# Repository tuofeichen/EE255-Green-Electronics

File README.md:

# EE255-Green-Electronics
This is the repo for the course project for EE 255 Green Electronics at Stanford. We built a prototype AC-AC converter system for load side demand response. 

Please see the below website for more information about the project. 
https://ee155powerprofiler.weebly.com

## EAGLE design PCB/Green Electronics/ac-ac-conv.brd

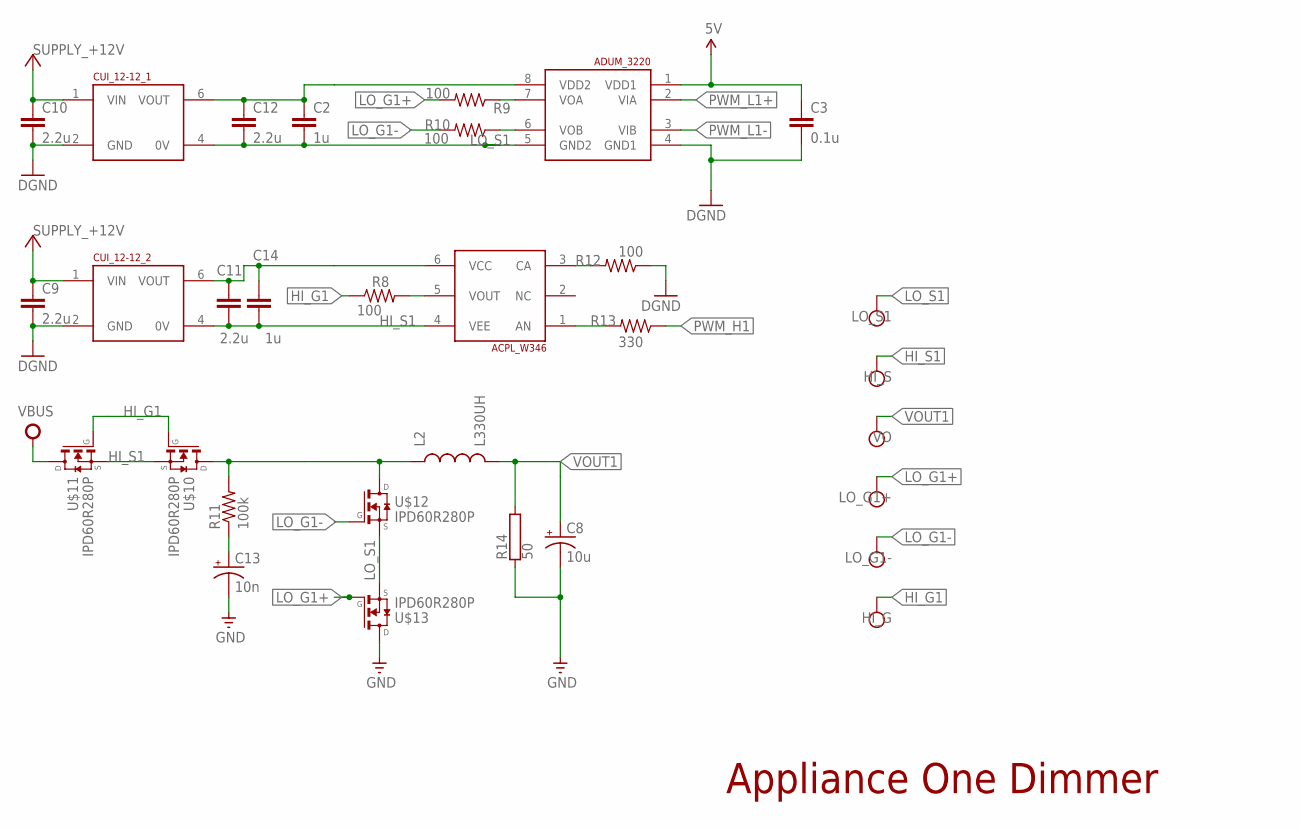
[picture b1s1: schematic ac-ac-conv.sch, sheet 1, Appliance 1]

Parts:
ACPL_W346: ACPL-W346-SSO6; SSO-6
ADUM_3220: ADUM3220; SO08
C2, C14: 1u; 0603-CAP
C3: 0.1u; 0603-CAP
C8: 10u; PANASONIC_C
C9, C10, C11, C12: 2.2u; 0603-CAP
C13: 10n; EIA3216
CUI_12-12_1, CUI_12-12_2: CUI-S12-S12; CUI_PDM2
HI_G: TESTPOINT0.1"; 1X01_ROUND
HI_S: TESTPOINT0.1"; 1X01_ROUND
L2: L330UH; BOUNRS_330UH
LO_G1+, LO_G1-: TESTPOINT0.1"; 1X01_ROUND
LO_S1: TESTPOINT0.1"; 1X01_ROUND
R8, R9, R10, R12: 100; 0603-RES
R11: 100k; R2512
R13: 330; 0603-RES
R14: 50; TO-247-2V
U$10, U$11, U$12, U$13: IPD60R280P; DPAK
VO: TESTPOINT0.1"; 1X01_ROUND

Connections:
5V: ADUM_3220.1 (VDD1), C3.1; also elsewhere on the board
+12V: C9.1, C10.1, CUI_12-12_1.1 (VIN), CUI_12-12_2.1 (VIN); also elsewhere on the board
GND: ADUM_3220.4 (GND1), C3.2, C8.-, C9.2, C10.2, C13.C (-), CUI_12-12_1.2 (GND), CUI_12-12_2.2 (GND), R12.1, R14.1, U$13.4 (D); also elsewhere on the board
HI_G1: HI_G.1, R8.1, U$10.1 (G), U$11.1 (G)
HI_PS1: ACPL_W346.6 (VCC), C11.1, C14.1, CUI_12-12_2.6 (VOUT)
HI_S1: ACPL_W346.4 (VEE), C11.2, C14.2, CUI_12-12_2.4 (0V), HI_S.1, U$10.3 (S), U$11.3 (S)
LO_G1+: LO_G1+.1, R9.2, U$13.1 (G)
LO_G1-: LO_G1-.1, R10.2, U$12.1 (G)
LO_PS1: ADUM_3220.8 (VDD2), C2.1, C12.1, CUI_12-12_1.6 (VOUT)
LO_S1: ADUM_3220.5 (GND2), C2.2, C12.2, CUI_12-12_1.4 (0V), LO_S1.1, U$12.3 (S), U$13.3 (S)
unnamed: L2.P$1 (1), R11.2, U$10.4 (D), U$12.4 (D)
unnamed: C13.A (+), R11.1
unnamed: ACPL_W346.3 (CA), R12.2
unnamed: ACPL_W346.1 (AN), R13.2
unnamed: ADUM_3220.7 (VOA), R9.1
unnamed: ADUM_3220.6 (VOB), R10.1
PWM_H1: R13.1; also elsewhere on the board
PWM_L1+: ADUM_3220.2 (VIA); also elsewhere on the board
PWM_L1-: ADUM_3220.3 (VIB); also elsewhere on the board
VBUS: U$11.4 (D); also elsewhere on the board
VOUT1: C8.+, L2.P$2 (2), R14.2, VO.1; also elsewhere on the board
VOUT_H2: ACPL_W346.5 (VOUT), R8.2

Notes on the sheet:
Appliance One Dimmer

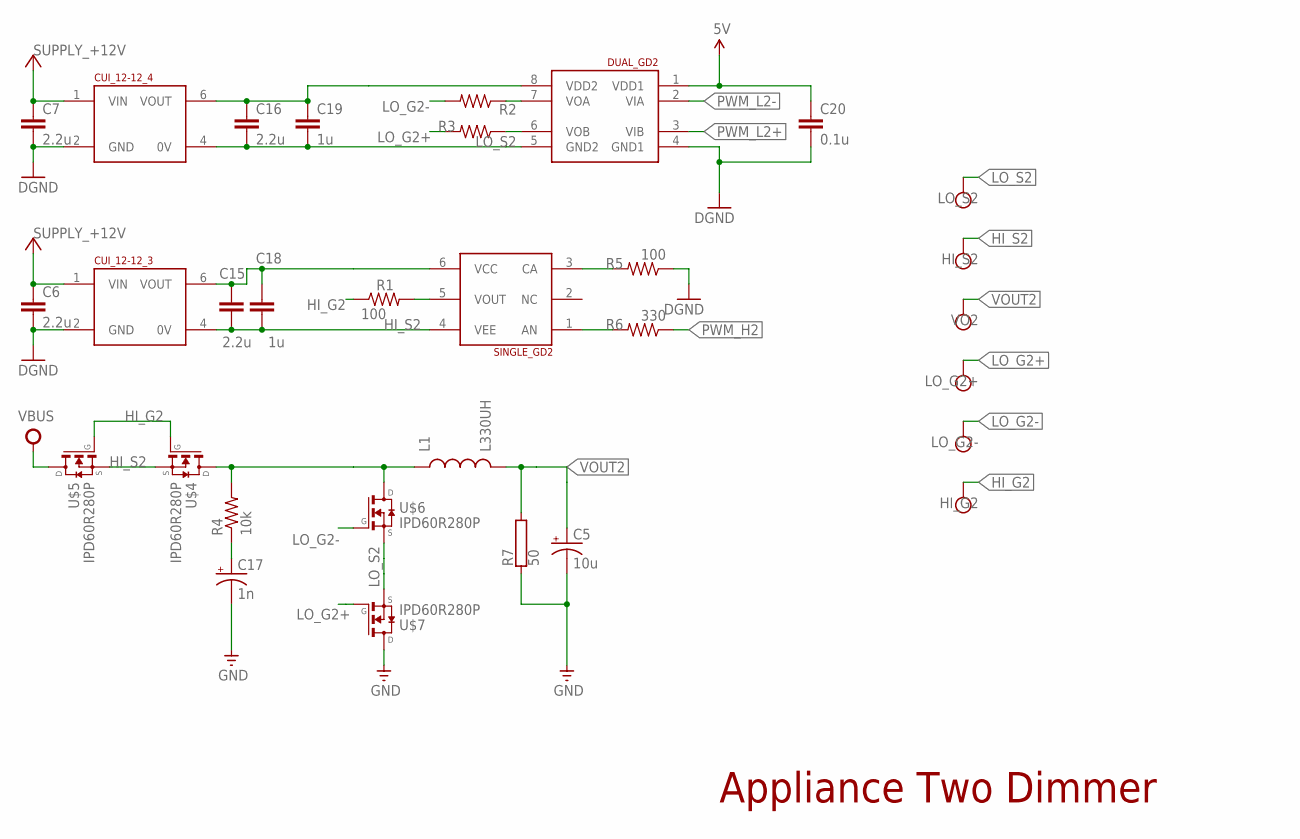
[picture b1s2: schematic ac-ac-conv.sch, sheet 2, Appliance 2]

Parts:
C5: 10u; PANASONIC_C
C6, C7, C15, C16: 2.2u; 0603-CAP
C17: 1n; EIA3216
C18, C19: 1u; 0603-CAP
C20: 0.1u; 0603-CAP
CUI_12-12_3, CUI_12-12_4: CUI-S12-S12; CUI_PDM2
DUAL_GD2: ADUM3220; SO08
HI_G2: TESTPOINT0.1"; 1X01_ROUND
HI_S2: TESTPOINT0.1"; 1X01_ROUND
L1: L330UH; BOUNRS_330UH
LO_G2+, LO_G2-: TESTPOINT0.1"; 1X01_ROUND
LO_S2: TESTPOINT0.1"; 1X01_ROUND
R1, R5: 100; 0603-RES
R2, R3: RESISTOR0603-RES; 0603-RES
R4: 10k; R2512
R6: 330; 0603-RES
R7: 50; TO-247-2V
SINGLE_GD2: ACPL-W346-SSO6; SSO-6
U$4, U$5, U$6, U$7: IPD60R280P; DPAK
VO2: TESTPOINT0.1"; 1X01_ROUND

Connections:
5V: C20.1, DUAL_GD2.1 (VDD1); also elsewhere on the board
+12V: C6.1, C7.1, CUI_12-12_3.1 (VIN), CUI_12-12_4.1 (VIN); also elsewhere on the board
GND: C5.-, C6.2, C7.2, C17.C (-), C20.2, CUI_12-12_3.2 (GND), CUI_12-12_4.2 (GND), DUAL_GD2.4 (GND1), R5.1, R7.1, U$7.4 (D); also elsewhere on the board
HI_G2: HI_G2.1, R1.1, U$4.1 (G), U$5.1 (G)
HI_PS2: C15.1, C18.1, CUI_12-12_3.6 (VOUT), SINGLE_GD2.6 (VCC)
HI_S2: C15.2, C18.2, CUI_12-12_3.4 (0V), HI_S2.1, SINGLE_GD2.4 (VEE), U$4.3 (S), U$5.3 (S)
LO_G2+: LO_G2+.1, R3.2, U$7.1 (G)
LO_G2-: LO_G2-.1, R2.2, U$6.1 (G)
LO_PS2: C16.1, C19.1, CUI_12-12_4.6 (VOUT), DUAL_GD2.8 (VDD2)
LO_S2: C16.2, C19.2, CUI_12-12_4.4 (0V), DUAL_GD2.5 (GND2), LO_S2.1, U$6.3 (S), U$7.3 (S)
unnamed: L1.P$1 (1), R4.2, U$4.4 (D), U$6.4 (D)
unnamed: C17.A (+), R4.1
unnamed: R5.2, SINGLE_GD2.3 (CA)
unnamed: R6.2, SINGLE_GD2.1 (AN)
unnamed: DUAL_GD2.7 (VOA), R2.1
unnamed: DUAL_GD2.6 (VOB), R3.1
PWM_H2: R6.1; also elsewhere on the board
PWM_L2+: DUAL_GD2.3 (VIB); also elsewhere on the board
PWM_L2-: DUAL_GD2.2 (VIA); also elsewhere on the board
VBUS: U$5.4 (D); also elsewhere on the board
VOUT2: C5.+, L1.P$2 (2), R7.2, VO2.1; also elsewhere on the board
VOUT_H1: R1.2, SINGLE_GD2.5 (VOUT)

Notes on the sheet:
Appliance Two Dimmer

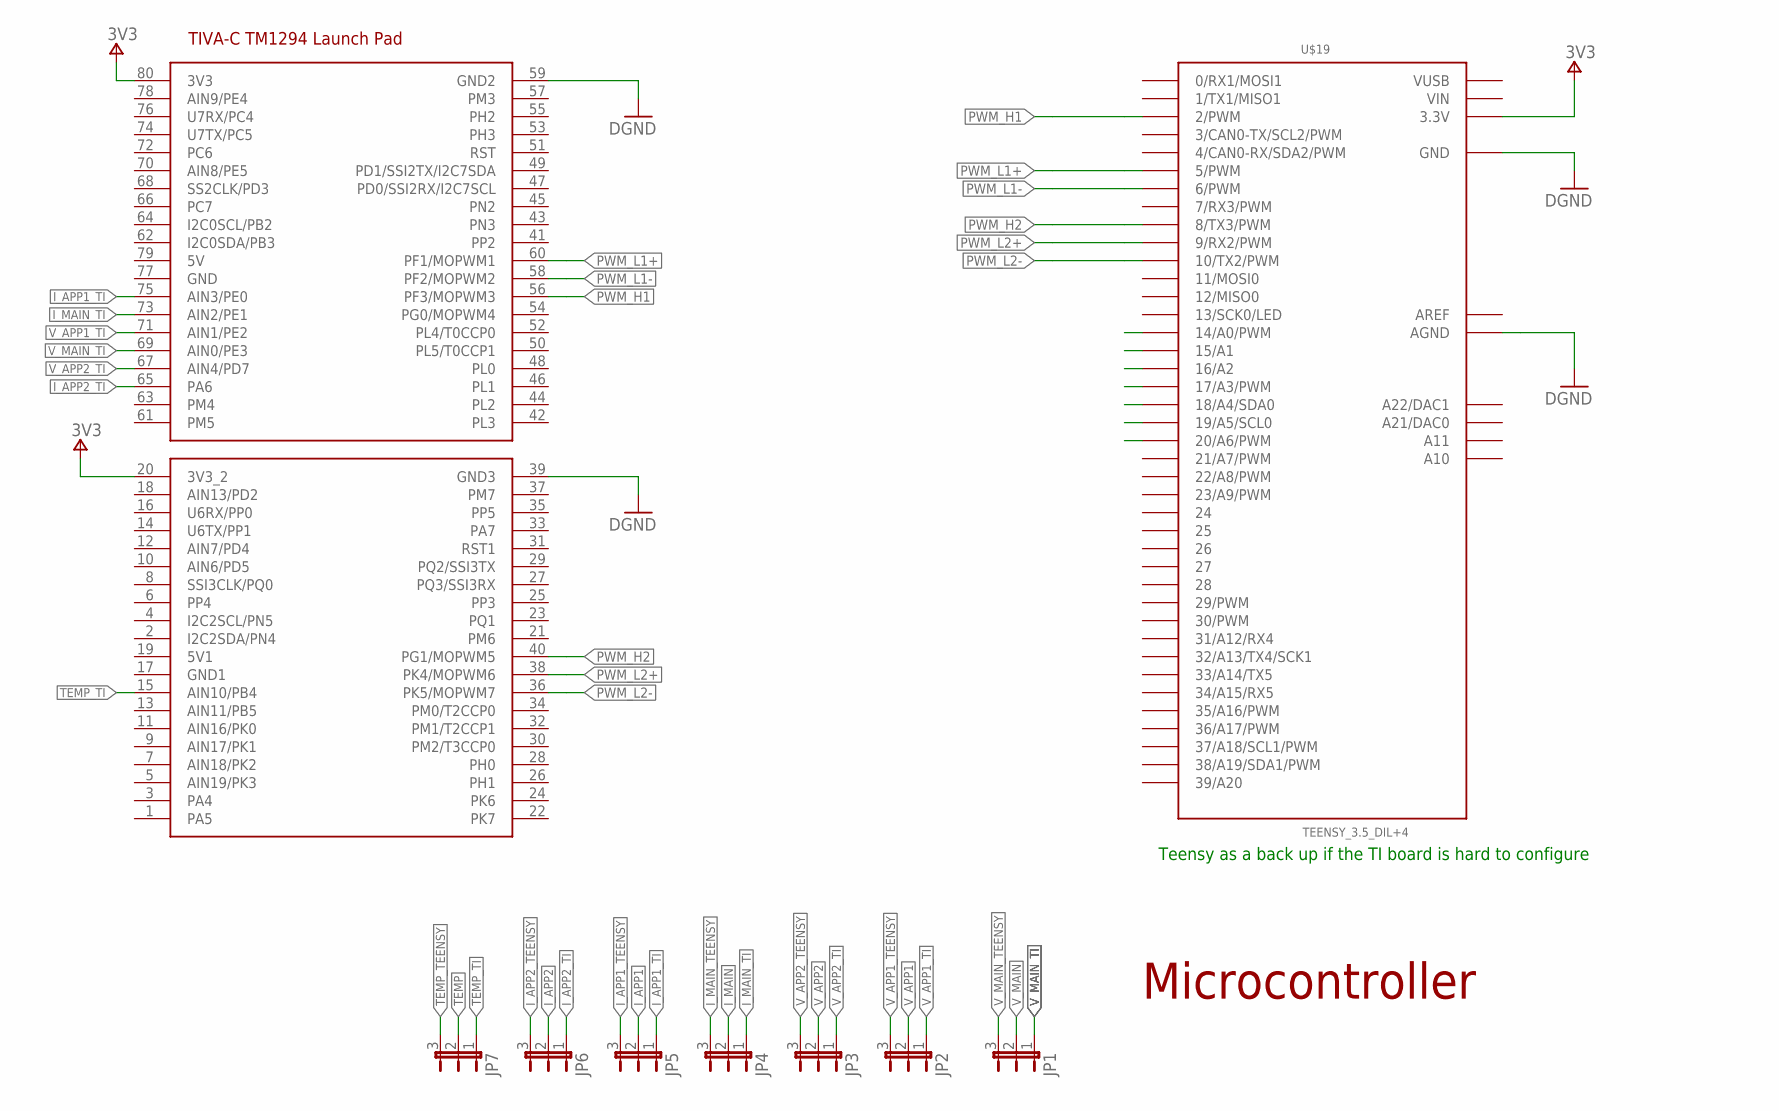
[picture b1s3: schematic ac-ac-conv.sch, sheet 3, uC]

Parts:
JP1, JP2, JP3, JP4, JP5, JP6, JP7: JUMPER-3SMD; SJ_3
U$17: TM4C1294_SHIELD; TIVA-C-LP-BOOSTER-PACK
U$19: TEENSY_3.5_DIL+4

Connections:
3V3: U$17.20 (3V3_2), U$17.80 (3V3), U$19.3.3V, U$19.3.3V3 (3.3V); also elsewhere on the board
AREF: U$19.AREF
GND: U$17.39 (GND3), U$17.59 (GND2), U$19.AGND, U$19.GND, U$19.GND1 (GND); also elsewhere on the board
I_APP1: JP5.2; also elsewhere on the board
I_APP1_TEENSY: JP5.3
I_APP1_TI: JP5.1, U$17.75 (AIN3/PE0)
I_APP2: JP6.2; also elsewhere on the board
I_APP2_TEENSY: JP6.3
I_APP2_TI: JP6.1, U$17.65 (PA6)
I_MAIN: JP4.2; also elsewhere on the board
I_MAIN_TEENSY: JP4.3
I_MAIN_TI: JP4.1, U$17.73 (AIN2/PE1)
PWM_H1: U$17.56 (PF3/MOPWM3), U$19.2 (2/PWM); also elsewhere on the board
PWM_H2: U$17.40 (PG1/MOPWM5), U$19.8 (8/TX3/PWM); also elsewhere on the board
PWM_L1+: U$17.60 (PF1/MOPWM1), U$19.5 (5/PWM); also elsewhere on the board
PWM_L1-: U$17.58 (PF2/MOPWM2), U$19.6 (6/PWM); also elsewhere on the board
PWM_L2+: U$17.38 (PK4/MOPWM6), U$19.9 (9/RX2/PWM); also elsewhere on the board
PWM_L2-: U$17.36 (PK5/MOPWM7), U$19.10 (10/TX2/PWM); also elsewhere on the board
TEMP: JP7.2; also elsewhere on the board
TEMP_TEENSY: JP7.3
TEMP_TI: JP7.1, U$17.15 (AIN10/PB4)
VIN: U$19.VIN
VUSB: U$19.VUSB
V_APP1: JP2.2; also elsewhere on the board
V_APP1_TEENSY: JP2.3
V_APP1_TI: JP2.1, U$17.71 (AIN1/PE2)
V_APP2: JP3.2; also elsewhere on the board
V_APP2_TEENSY: JP3.3
V_APP2_TI: JP3.1, U$17.67 (AIN4/PD7)
V_MAIN: JP1.2; also elsewhere on the board
V_MAIN_TEENSY: JP1.3
V_MAIN_TI: JP1.1, U$17.69 (AIN0/PE3)

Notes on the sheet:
Teensy as a back up if the TI board is hard to configure
Microcontroller

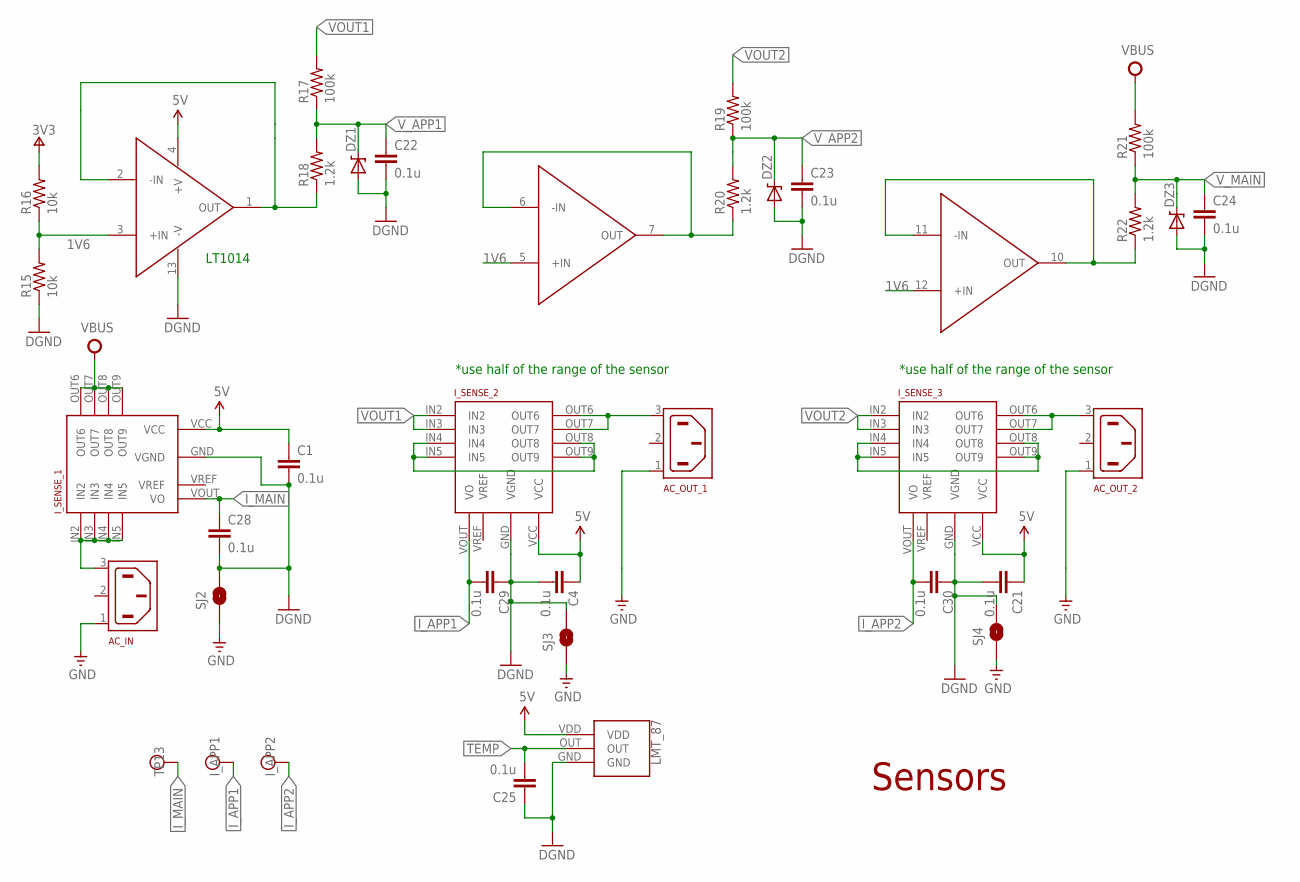
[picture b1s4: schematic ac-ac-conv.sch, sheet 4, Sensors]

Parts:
AC_IN: 6ESRM-P
AC_OUT_1, AC_OUT_2: 6ESRM-P
C1, C4, C21, C22, C23, C24, C25, C28, C29, C30: 0.1u; 0603-CAP
DZ1, DZ2, DZ3: DIODE-ZENER-BZT52; SOD-323
I_APP1, I_APP2: TESTPOINT0.1"; 1X01_ROUND
I_SENSE_1, I_SENSE_2, I_SENSE_3: F03PS05; F03P_THRU_HOLE
LMT_87: LMT87_PAC; LMT87_TO
R15, R16: 10k; 0603-RES
R17, R19, R21: 100k; 1206
R18, R20, R22: 1.2k; 1206
SJ2, SJ3, SJ4: SOLDERJUMPERNC2; SJ_2S-NOTRACE
TP13: TESTPOINT0.1"; 1X01_ROUND
U$15: LT1014; SO16L

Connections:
1V6: R15.2, R16.1, U$15.3 (+IN), U$15.5 (+IN), U$15.12 (+IN)
3V3: R16.2; also elsewhere on the board
5V: C1.1, C4.1, C21.1, I_SENSE_1.VCC, I_SENSE_2.VCC, I_SENSE_3.VCC, LMT_87.VDD, U$15.4 (+V); also elsewhere on the board
+IN: U$15.14 (+IN)
-IN: U$15.15 (-IN)
DGND: C1.2, C4.2, C21.2, C28.2, C29.1, C30.1, I_SENSE_1.GND (VGND), I_SENSE_2.GND (VGND), I_SENSE_3.GND (VGND), SJ2.2, SJ3.2, SJ4.2
GND: AC_IN.1 (AC1), AC_OUT_1.1 (AC1), AC_OUT_2.1 (AC1), C22.2, C23.2, C24.2, C25.1, DZ1.2 (A), DZ2.2 (A), DZ3.2 (A), LMT_87.GND, R15.1, SJ2.1, SJ3.1, SJ4.1, U$15.13 (-V); also elsewhere on the board
I_APP1: C29.2, I_APP1.1, I_SENSE_2.VOUT (VO); also elsewhere on the board
I_APP2: C30.2, I_APP2.1, I_SENSE_3.VOUT (VO); also elsewhere on the board
I_MAIN: C28.1, I_SENSE_1.VOUT (VO), TP13.1; also elsewhere on the board
unnamed: AC_IN.3 (AC2), I_SENSE_1.IN2, I_SENSE_1.IN3, I_SENSE_1.IN4, I_SENSE_1.IN5
unnamed: I_SENSE_2.IN4, I_SENSE_2.IN5, I_SENSE_2.OUT8, I_SENSE_2.OUT9
unnamed: I_SENSE_3.IN4, I_SENSE_3.IN5, I_SENSE_3.OUT8, I_SENSE_3.OUT9
unnamed: AC_OUT_1.3 (AC2), I_SENSE_2.OUT6, I_SENSE_2.OUT7
unnamed: AC_OUT_2.3 (AC2), I_SENSE_3.OUT6, I_SENSE_3.OUT7
unnamed: R18.1, U$15.1 (OUT), U$15.2 (-IN)
unnamed: R22.1, U$15.10 (OUT), U$15.11 (-IN)
unnamed: R20.1, U$15.6 (-IN), U$15.7 (OUT)
OUT: U$15.16 (OUT)
TEMP: C25.2, LMT_87.OUT; also elsewhere on the board
VBUS: I_SENSE_1.OUT6, I_SENSE_1.OUT7, I_SENSE_1.OUT8, I_SENSE_1.OUT9, R21.2; also elsewhere on the board
VOUT1: I_SENSE_2.IN2, I_SENSE_2.IN3, R17.2; also elsewhere on the board
VOUT2: I_SENSE_3.IN2, I_SENSE_3.IN3, R19.2; also elsewhere on the board
V_APP1: C22.1, DZ1.1 (C), R17.1, R18.2; also elsewhere on the board
V_APP2: C23.1, DZ2.1 (C), R19.1, R20.2; also elsewhere on the board
V_MAIN: C24.1, DZ3.1 (C), R21.1, R22.2; also elsewhere on the board

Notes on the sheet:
*use half of the range of the sensor
LT1014
Sensors

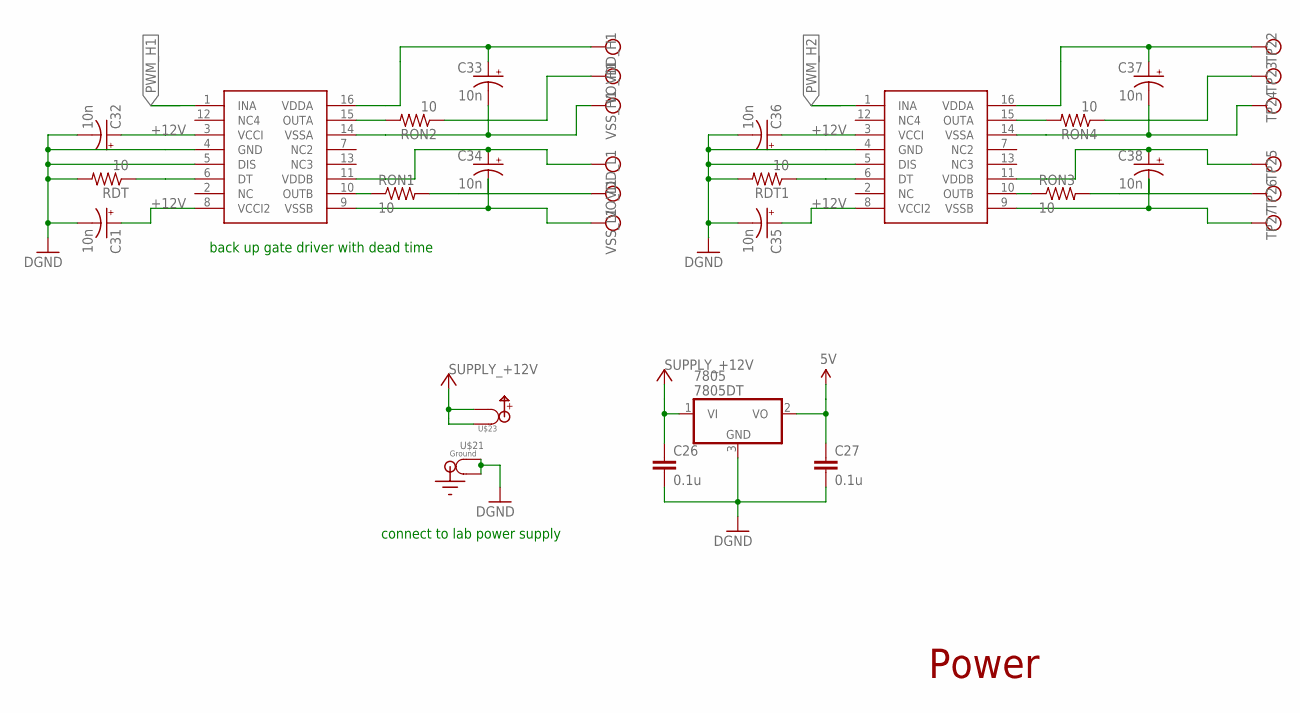
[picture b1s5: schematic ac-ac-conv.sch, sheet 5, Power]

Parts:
7805: 7805DT; TO252
C26, C27: 0.1u; 0603-CAP
C31, C32, C33, C34, C35, C36, C37, C38: 10n; EIA3216
RDT, RDT1: 10; 0603-RES
RON1, RON2, RON3, RON4: 10; 0603-RES
TP22, TP23, TP24, TP25, TP26, TP27: TESTPOINT0.1"; 1X01_ROUND
U$1, U$9: UCC20520; SO16
U$21: SPADE-GROUND
U$23: SPADE-POWER
VDD_H1: TESTPOINT0.1"; 1X01_ROUND
VDD_L1: TESTPOINT0.1"; 1X01_ROUND
VO_H1: TESTPOINT0.1"; 1X01_ROUND
VO_L1: TESTPOINT0.1"; 1X01_ROUND
VSS_H1: TESTPOINT0.1"; 1X01_ROUND
VSS_L1: TESTPOINT0.1"; 1X01_ROUND

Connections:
5V: 7805.2 (VO), C27.1; also elsewhere on the board
+12V: 7805.1 (VI), C26.1, C31.A (+), C32.A (+), C35.A (+), C36.A (+), U$1.3 (VCCI), U$1.8 (VCCI2), U$9.3 (VCCI), U$9.8 (VCCI2), U$23.P$1, U$23.P$2; also elsewhere on the board
GND: 7805.3 (GND), C26.2, C27.2, C31.C (-), C32.C (-), C35.C (-), C36.C (-), RDT.2, RDT1.2, U$1.4 (GND), U$1.5 (DIS), U$9.4 (GND), U$9.5 (DIS), U$21.P$1, U$21.P$2; also elsewhere on the board
unnamed: C33.A (+), U$1.16 (VDDA), VDD_H1.1
unnamed: RON1.1, U$1.10 (OUTB)
unnamed: RDT.1, U$1.6 (DT)
unnamed: C33.C (-), U$1.14 (VSSA), VSS_H1.1
unnamed: C34.A (+), U$1.11 (VDDB), VDD_L1.1
unnamed: RON1.2, VO_L1.1
unnamed: C34.C (-), U$1.9 (VSSB), VSS_L1.1
unnamed: RON2.2, U$1.15 (OUTA)
unnamed: RON2.1, VO_H1.1
unnamed: RDT1.1, U$9.6 (DT)
unnamed: C37.A (+), TP22.1, U$9.16 (VDDA)
unnamed: C37.C (-), TP24.1, U$9.14 (VSSA)
unnamed: C38.C (-), TP27.1, U$9.9 (VSSB)
unnamed: C38.A (+), TP25.1, U$9.11 (VDDB)
unnamed: RON3.1, U$9.10 (OUTB)
unnamed: RON3.2, TP26.1
unnamed: RON4.2, U$9.15 (OUTA)
unnamed: RON4.1, TP23.1
PWM_H1: U$1.1 (INA); also elsewhere on the board
PWM_H2: U$9.1 (INA); also elsewhere on the board

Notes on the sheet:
connect to lab power supply
Power
back up gate driver with dead time

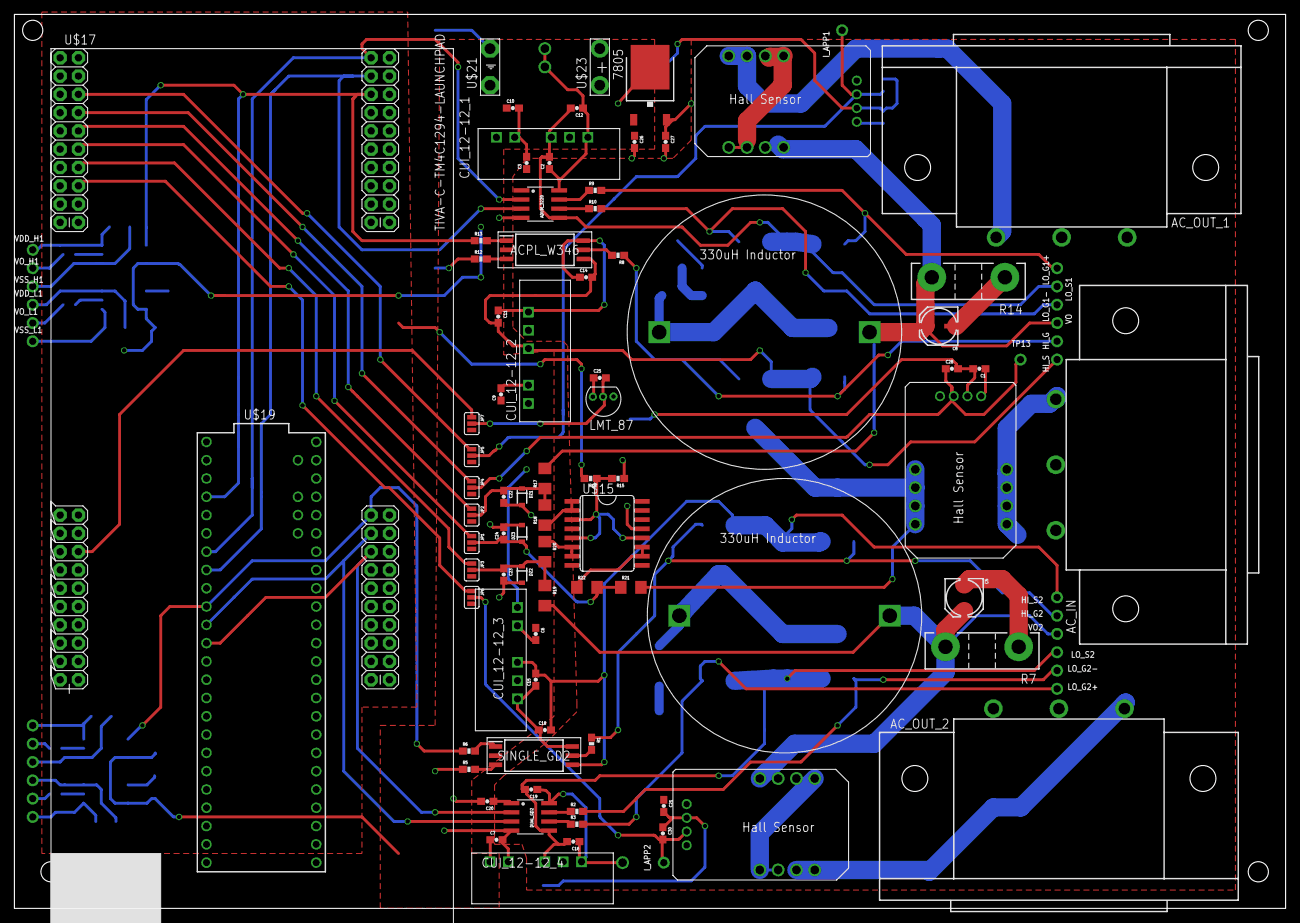
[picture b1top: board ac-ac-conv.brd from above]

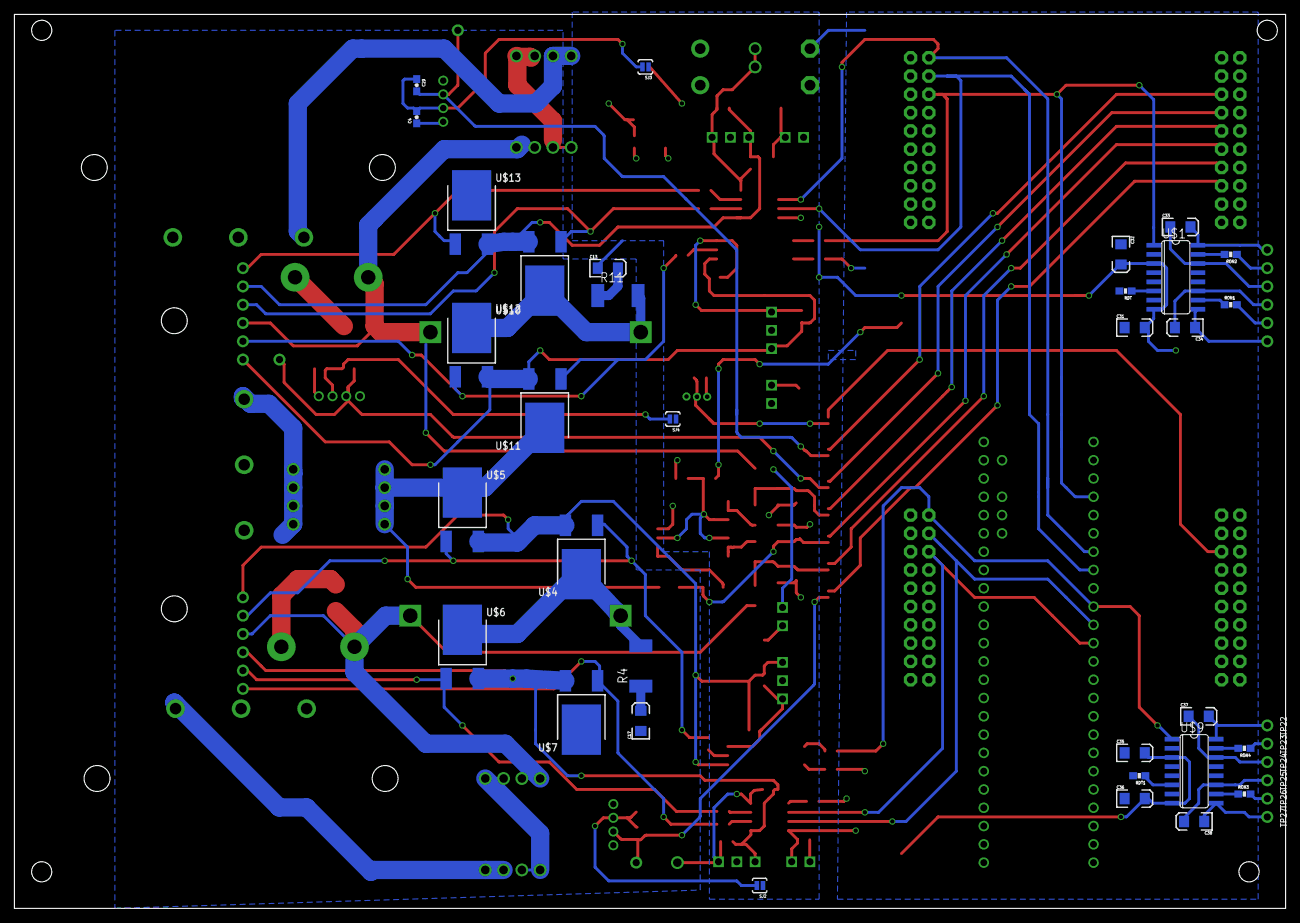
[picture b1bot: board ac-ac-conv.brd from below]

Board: 2 copper layers, 176.5 x 124.1 mm, 139 parts (39 on the bottom side), 83 nets.

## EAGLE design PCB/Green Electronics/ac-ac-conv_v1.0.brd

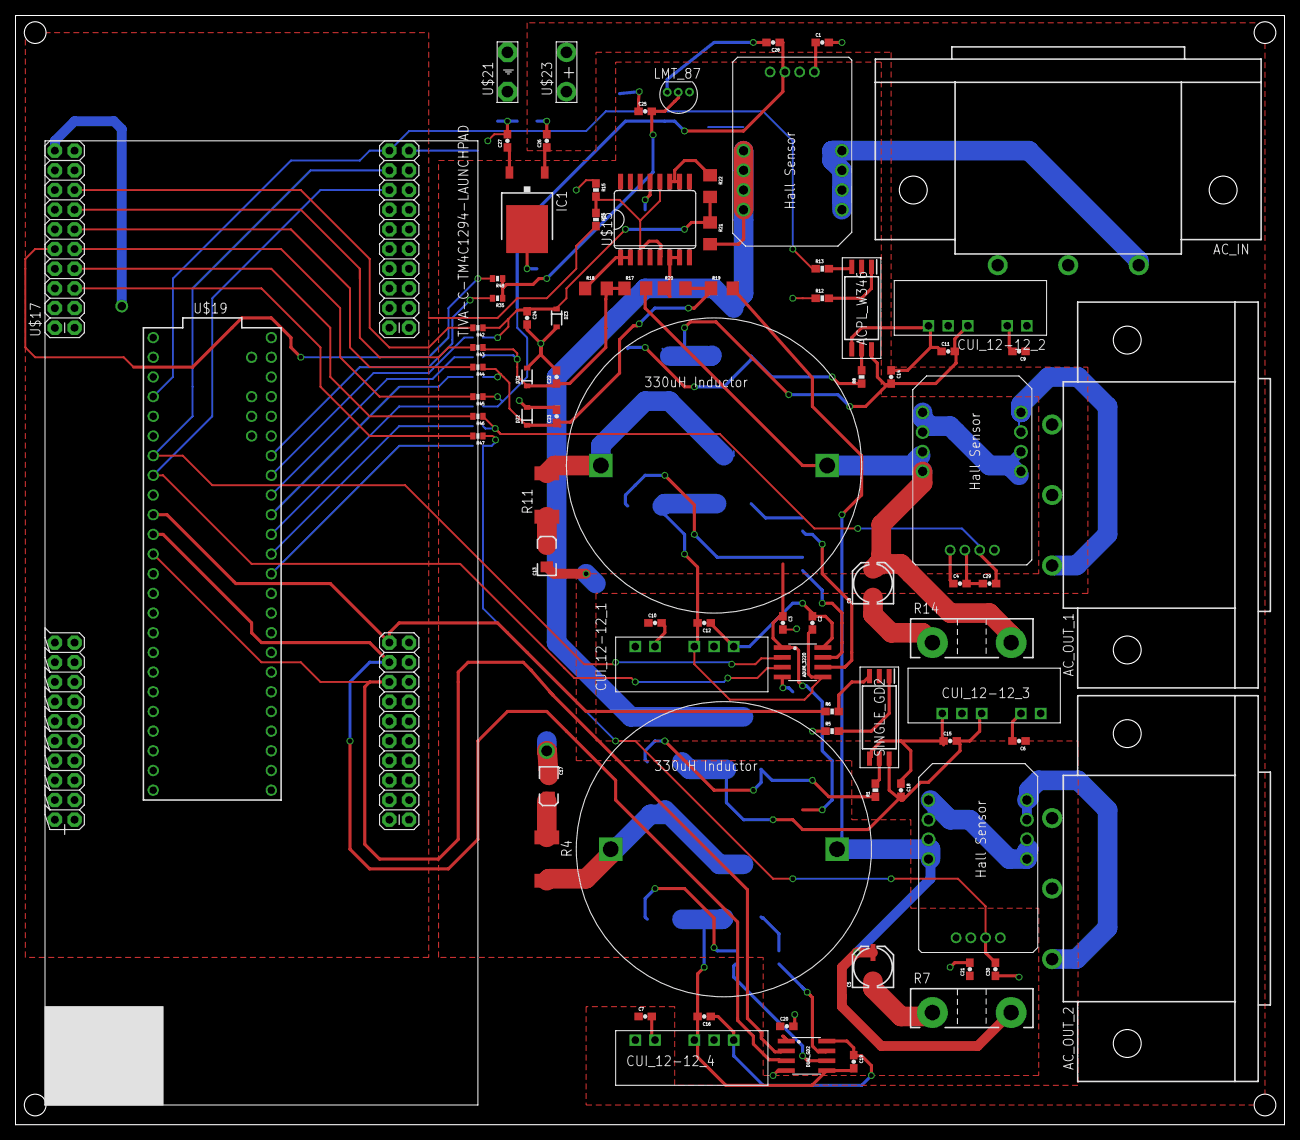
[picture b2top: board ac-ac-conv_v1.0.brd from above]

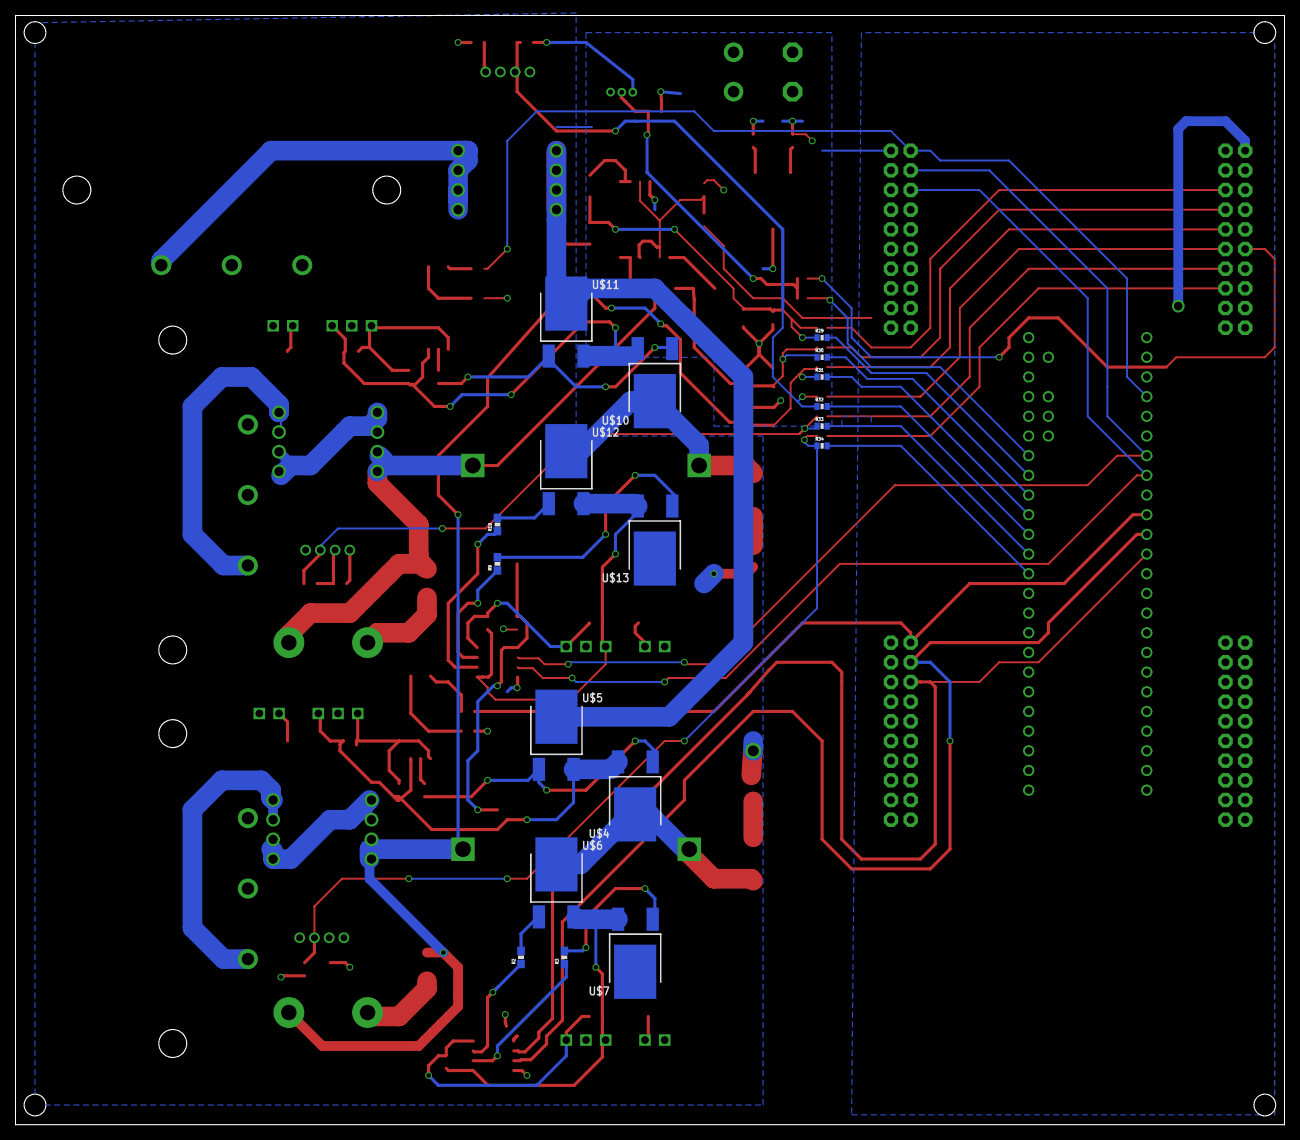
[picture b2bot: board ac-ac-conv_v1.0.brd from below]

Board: 2 copper layers, 163.8 x 143.2 mm, 100 parts (18 on the bottom side), 71 nets.

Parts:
ACPL_W346: ACPL-W346-SSO6; SSO-6
AC_IN: 6ESRM-P
AC_OUT_1, AC_OUT_2: 6ESRM-P
ADUM_3220: ADUM3220; SO08
C1, C3, C4, C20, C21, C22, C23, C24, C25, C26, C27, C28, C29, C30: 0.1u; 0603-CAP
C2, C14, C18, C19: 1u; 0603-CAP
C5, C8: 10u; PANASONIC_C
C6, C7, C9, C10, C11, C12, C15, C16: 2.2u; 0603-CAP
C13: 10n; EIA3216
C17: 1n; EIA3216
CUI_12-12_1, CUI_12-12_2, CUI_12-12_3, CUI_12-12_4: CUI-S12-S12; CUI_PDM2
DUAL_GD2: ADUM3220; SO08
DZ1, DZ2, DZ3: DIODE-ZENER-BZT52; SOD-323
IC1: 7805DT; TO252
I_SENSE_1, I_SENSE_2, I_SENSE_3: F03PS05; F03P_THRU_HOLE
L1, L2: L330UH; BOUNRS_330UH
LMT_87: LMT87_PAC; LMT87_TO
R1, R5, R8, R9, R10, R12: 100; 0603-RES
R2, R3: 0603-RES
R4: 10k; R2512
R6, R13: 330; 0603-RES
R7, R14: 50; TO-247-2V
R11: 100k; R2512
R15, R16: 10k; 0603-RES
R17, R19, R21: 100k; 1206
R18, R20, R22: 1.2k; 1206
R29, R30, R31, R32, R33, R34, R35, R42, R43, R44, R45, R46, R47, R48: 0402-RES
SINGLE_GD2: ACPL-W346-SSO6; SSO-6
U$4, U$5, U$6, U$7, U$10, U$11, U$12, U$13: IPD60R280P; DPAK
U$15: LT1014; SO16L
U$17: TM4C1294_SHIELD; TIVA-C-LP-BOOSTER-PACK
U$19: TEENSY_3.5_DIL+4
U$21: SPADE-GROUND
U$23: SPADE-POWER

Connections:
1V6: R15.2, R16.1, U$15.3, U$15.5, U$15.12
3V3: R16.2, U$17.20, U$17.80, U$19.3.3V, U$19.3.3V3
5V: ADUM_3220.1, C1.1, C3.1, C4.1, C20.1, C21.1, C27.1, DUAL_GD2.1, IC1.2, I_SENSE_1.VCC, I_SENSE_2.VCC, I_SENSE_3.VCC, LMT_87.VDD, U$15.4
+12V: C6.1, C7.1, C9.1, C10.1, C26.1, CUI_12-12_1.1, CUI_12-12_2.1, CUI_12-12_3.1, CUI_12-12_4.1, IC1.1, U$23.P$1, U$23.P$2
GND: AC_IN.3, AC_OUT_1.3, AC_OUT_2.3, ADUM_3220.4, C1.2, C3.2, C4.2, C5.-, C6.2, C7.2, C8.-, C9.2, C10.2, C13.C, C17.C, C20.2, C21.2, C22.2, C23.2, C24.2, C25.1, C26.2, C27.2, C28.2, C29.1, C30.1, CUI_12-12_1.2, CUI_12-12_2.2, CUI_12-12_3.2, CUI_12-12_4.2, DUAL_GD2.4, DZ1.2, DZ2.2, DZ3.2, IC1.3, I_SENSE_1.GND, I_SENSE_2.GND, I_SENSE_3.GND, LMT_87.GND, R5.1, R7.1, R12.1, R14.1, R15.1, U$7.4, U$13.4, U$15.13, U$17.39, U$17.59, U$19.AGND, U$19.GND, U$19.GND1, U$21.P$1, U$21.P$2
HI_G1: R8.1, U$10.1, U$11.1
HI_G2: R1.1, U$4.1, U$5.1
HI_PS1: ACPL_W346.4, C11.1, C14.1, CUI_12-12_2.6
HI_PS2: C15.1, C18.1, CUI_12-12_3.6, SINGLE_GD2.4
HI_S1: ACPL_W346.6, C11.2, C14.2, CUI_12-12_2.4, U$10.3, U$11.3
HI_S2: C15.2, C18.2, CUI_12-12_3.4, SINGLE_GD2.6, U$4.3, U$5.3
I_APP1: C29.2, I_SENSE_2.VOUT, R33.1, R46.1
I_APP2: C30.2, I_SENSE_3.VOUT, R34.1, R47.1
I_MAIN: C28.1, I_SENSE_1.VOUT, R32.1, R45.1
LO_G1+: R9.2, U$13.1
LO_G1-: R10.2, U$12.1
LO_G2+: R3.2, U$7.1
LO_G2-: R2.2, U$6.1
LO_PS1: ADUM_3220.8, C2.1, C12.1, CUI_12-12_1.6
LO_PS2: C16.1, C19.1, CUI_12-12_4.6, DUAL_GD2.8
LO_S1: ADUM_3220.5, C2.2, C12.2, CUI_12-12_1.4, U$12.3, U$13.3
LO_S2: C16.2, C19.2, CUI_12-12_4.4, DUAL_GD2.5, U$6.3, U$7.3
unnamed: AC_IN.1, I_SENSE_1.IN2, I_SENSE_1.IN3, I_SENSE_1.IN4, I_SENSE_1.IN5
unnamed: I_SENSE_2.IN4, I_SENSE_2.IN5, I_SENSE_2.OUT8, I_SENSE_2.OUT9
unnamed: I_SENSE_3.IN4, I_SENSE_3.IN5, I_SENSE_3.OUT8, I_SENSE_3.OUT9
unnamed: AC_OUT_1.1, I_SENSE_2.OUT6, I_SENSE_2.OUT7
unnamed: L1.P$1, R4.2, U$4.4, U$6.4
unnamed: C17.A, R4.1
unnamed: R5.2, SINGLE_GD2.1
unnamed: R6.2, SINGLE_GD2.3
unnamed: L2.P$1, R11.2, U$10.4, U$12.4
unnamed: AC_OUT_2.1, I_SENSE_3.OUT6, I_SENSE_3.OUT7
unnamed: C13.A, R11.1
unnamed: ACPL_W346.1, R12.2
unnamed: ACPL_W346.3, R13.2
unnamed: ADUM_3220.7, R9.1
unnamed: R18.1, U$15.1, U$15.2
unnamed: R34.2, U$19.14/A0
unnamed: R22.1, U$15.10, U$15.11
unnamed: R33.2, U$19.15/A1
unnamed: R20.1, U$15.6, U$15.7
unnamed: R32.2, U$19.16/A2
unnamed: R31.2, U$19.17/A3
unnamed: ADUM_3220.6, R10.1
unnamed: DUAL_GD2.7, R2.1
unnamed: R30.2, U$19.18/A4
unnamed: DUAL_GD2.6, R3.1
unnamed: R29.2, U$19.19/A5
unnamed: R35.2, U$19.20/A6
unnamed: R42.2, U$17.75
unnamed: R43.2, U$17.73
unnamed: R44.2, U$17.71
unnamed: R45.2, U$17.69
unnamed: R46.2, U$17.67
unnamed: R47.2, U$17.65
unnamed: R48.2, U$17.70
PWM_H1: R13.1, U$17.60, U$19.2
PWM_H2: R6.1, U$17.40, U$19.8
PWM_L1+: ADUM_3220.2, U$17.58, U$19.5
PWM_L1-: ADUM_3220.3, U$17.56, U$19.6
PWM_L2+: DUAL_GD2.3, U$17.38, U$19.9
PWM_L2-: DUAL_GD2.2, U$17.36, U$19.10
TEMP: C25.2, LMT_87.OUT, R35.1, R48.1
VBUS: I_SENSE_1.OUT6, I_SENSE_1.OUT7, I_SENSE_1.OUT8, I_SENSE_1.OUT9, R21.2, U$5.4, U$11.4
VOUT1: C8.+, I_SENSE_2.IN2, I_SENSE_2.IN3, L2.P$2, R14.2, R17.2
VOUT2: C5.+, I_SENSE_3.IN2, I_SENSE_3.IN3, L1.P$2, R7.2, R19.2
VOUT_H1: R1.2, SINGLE_GD2.5
VOUT_H2: ACPL_W346.5, R8.2
V_APP1: C22.1, DZ1.1, R17.1, R18.2, R30.1, R43.1
V_APP2: C23.1, DZ2.1, R19.1, R20.2, R31.1, R44.1
V_MAIN: C24.1, DZ3.1, R21.1, R22.2, R29.1, R42.1

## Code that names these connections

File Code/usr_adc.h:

/*
 * usr_adc.h
 *
 *  Created on: Nov 25, 2017
 *      Author: chentuofei
 */

#ifndef USR_ADC_H_
#define USR_ADC_H_

#include <stdint.h>
#include <stdbool.h>
#include "inc/hw_memmap.h"
#include "inc/hw_types.h"
#include "utils/uartstdio.h"
#include "driverlib/pin_map.h"
#include "driverlib/sysctl.h"
#include "driverlib/gpio.h"
#include "driverlib/adc.h"

#define I_MAIN_PIN ADC_CTL_CH2
#define I_APP1_PIN ADC_CTL_CH3
#define I_APP2_PIN ADC_CTL_CH8 // this originally connected to PA6

#define V_MAIN_PIN ADC_CTL_CH0
#define V_APP1_PIN ADC_CTL_CH4
#define V_APP2_PIN ADC_CTL_CH1

#define TEMP_SENS_PIN ADC_CTL_CH10



// sequencer to be used for initialization
void adc_init(int seq);
int adc_read(int seq,int chan);
void adc_calibrate(int num);

// sensor readings
extern int v_sense_main;
extern int v_sense_app1;
extern int v_sense_app2;
extern int i_sense_main;
extern int i_sense_app1;
extern int i_sense_app2;

extern int v_main_offset;
extern int v_app1_offset;
extern int v_app2_offset;


// max values of each cycle to compute the rms
extern int v_max_main;
extern int v_max_app1;
extern int v_max_app2;
extern int i_max_main;
extern int i_max_app1;
extern int i_max_app2;

extern float pwr_main;
extern float pwr_app1;
extern float pwr_app2;

#endif /* USR_ADC_H_ */

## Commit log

2017-10-05 add most recent code
2017-10-05 git cheat sheet
2017-10-07 calibration for energy meter
2017-12-15 final project
2017-12-16 add spice and pcb

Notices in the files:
parts and their libraries:
SparkFun-AnalogIC: Licensing:Creative Commons ShareAlike 4.0 International - https://creativecommons.org/licenses/by-sa/4.0
microbuilder: This work is placed in the public domain, and may be freely used for commercial and non-commercial work with the following conditions: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
